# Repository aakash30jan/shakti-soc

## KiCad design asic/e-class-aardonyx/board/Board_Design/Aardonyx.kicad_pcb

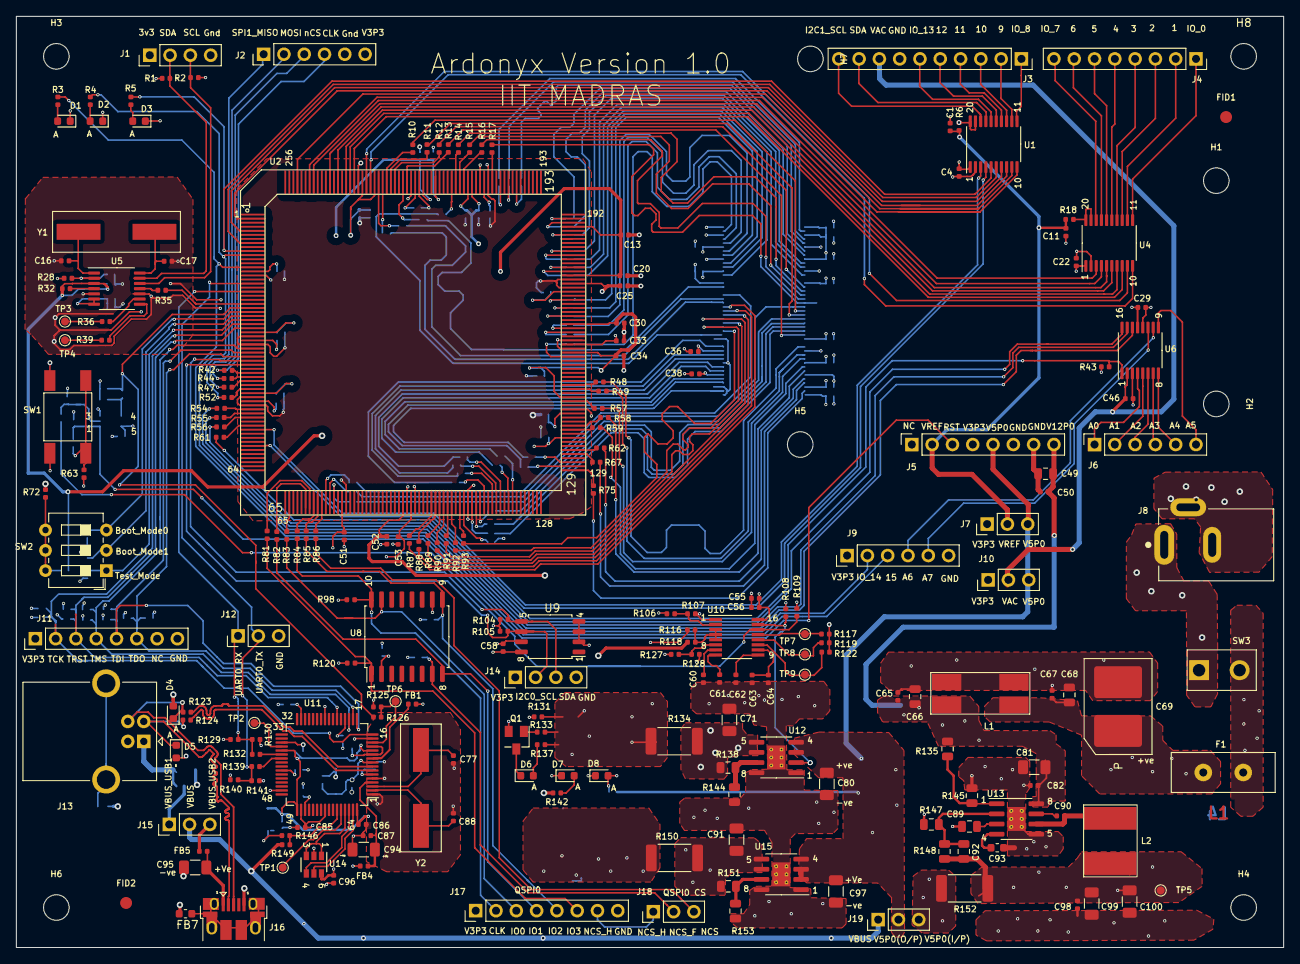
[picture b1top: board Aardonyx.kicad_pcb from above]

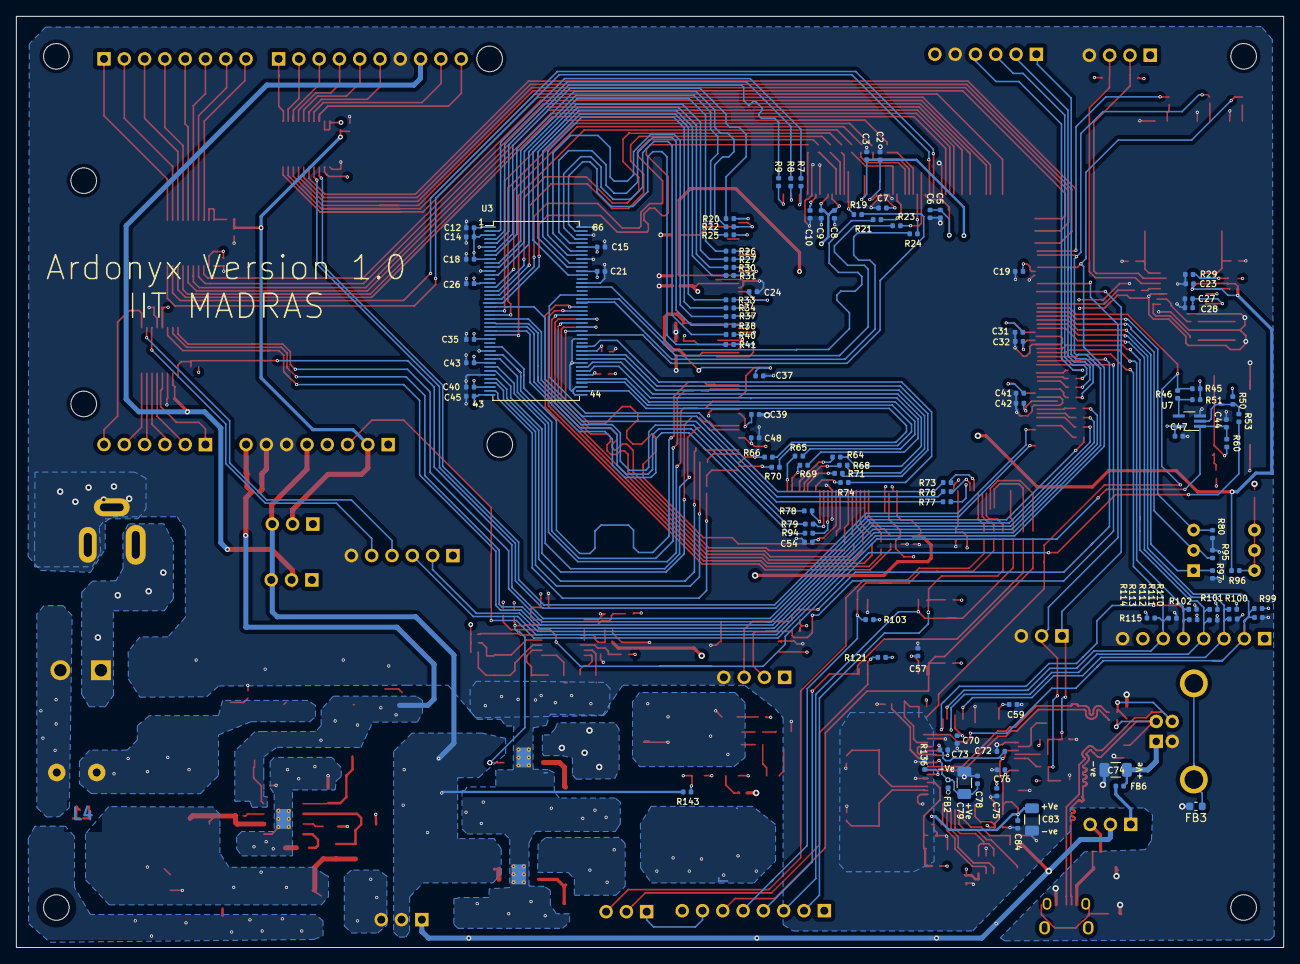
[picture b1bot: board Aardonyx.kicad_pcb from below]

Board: 4 copper layers, 158.6 x 116.5 mm, 330 parts (109 on the bottom side), 287 nets.

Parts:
C1, C2, C3, C4, C5, C6, C7, C8, C9, C10, C11, C12, C13, C14, C15, C18, C19, C20, C21, C22, C23, C24, C25, C26, C27, C28, C29, C30, C31, C32, C33, C34, C35, C36, C37, C38, C39, C40, C41, C42, C43, C44, C45, C46, C47, C48, C50, C51, C52, C53, C54, C55, C56, C57, C58, C59, C60, C61, C62, C63, C64, C65, C67, C70, C72, C73, C75, C76, C78, C82, C84, C85, C86, C87, C90, C96, C98: 0.1UF,0402; C_0402_1005Metric
C16, C17, C77, C88: 18PF,0402; C_0402_1005Metric
C49, C66, C68, C89: 1UF,0805; C_0805_2012Metric
C69: 220UF,2924; CP_EIA-2924_tcn4227_Pad6.1x7.3mm
C71, C91: 10UF,1206; C_1206_3216Metric
C74, C79, C80, C83, C94, C95, C97: 4.7UF,1206; C_1206_3216Metric
C81, C99, C100: 22UF,1206; C_1206_3216Metric
C92: 15PF,0805; C_0805_2012Metric
C93: 7500PF,0603; C_0603_1608Metric
D1, D2, D3, D6, D7, D8: LED,1206; LED_0603_1608Metric
D4, D5: CG0603MLC-12E; D_0603_1608Metric
F1: PTCCL13H921DBE; vishay_ptccl_d12.5mm_w4mm
FB1, FB2, FB4, FB5, FB6: 600E,FB,0402; L_0402_1005Metric
FB3, FB7: 47E,FB,0603; C_0603_1608Metric
FID1, FID2: Fiducial; Fiducial_1.5mm_Mask3mm
H1, H2, H3, H4, H5, H6, H7, H8: MountingHole; MountingHole_3.2mm_M3
J1, J14: Conn_1x4; PinHeader_1x04_P2.54mm_Vertical
J2, J9: Conn_1x6; PinHeader_1x06_P2.54mm_Vertical
J3: Conn_1x10_F; PinSocket_1x10_P2.54mm_Vertical
J4, J5: Conn_1x8_F; PinSocket_1x08_P2.54mm_Vertical
J6: Conn_1x6_F; PinSocket_1x06_P2.54mm_Vertical
J7, J10, J12, J15, J18, J19: Conn_1x3_M; PinHeader_1x03_P2.54mm_Vertical
J8: PJ-202H PWRJACK; CUI_PJ-202AH
J11, J17: Conn_1x8; PinHeader_1x08_P2.54mm_Vertical
J13: USB_B_6PIN; USB_B_OST_USB-B1HSxx_Horizontal
J16: USB_OTG; USB_Micro-B_Amphenol_10103594-0001LF_Horizontal
L1: CM3421Y600R-10; L_Laird_L9.55_W2.84
L2: 3.3UH; Bourns_srn8040ta_L8.5_W6.6
Q1: FDN339AN; SuperSOT-3
R1, R2, R28, R29, R32, R63, R106, R118, R128, R149: 4.7KE,0402; R_0402_1005Metric
R3, R4, R5, R142: 220E,0402; R_0402_1005Metric
R6, R18: 200KE,0402; R_0402_1005Metric
R7, R8, R9, R10, R11, R12, R13, R14, R15, R16, R17, R19, R20, R21, R22, R23, R24, R25, R26, R27, R30, R31, R33, R34, R35, R36, R37, R38, R39, R40, R41, R42, R44, R47, R48, R49, R52, R54, R55, R56, R57, R58, R59, R61, R62, R64, R65, R66, R67, R68, R69, R70, R71, R73, R74, R75, R76, R77, R78, R79, R81, R82, R83, R84, R85, R86, R87, R88, R89, R90, R91, R92, R93, R94, R123, R124: 22E,0402; R_0402_1005Metric
R43, R45, R50, R51, R80, R95, R97, R98, R103, R104, R105, R108, R109, R117, R119, R120, R121, R122, R146: 10KE,0402; R_0402_1005Metric
R46, R53, R72, R96, R126, R132, R139: 0E, 0402; R_0402_1005Metric
R60, R99, R100, R101, R102, R110, R111, R112, R113, R114, R115, R125, R129, R130, R131, R133, R140, R141, R143: 1KE,0402; R_0402_1005Metric
R107: 3.3kE, 0402; R_0402_1005Metric
R116, R127: 1.2kE, 0402; R_0402_1005Metric
R134, R150, R152: 0.02E,2512; R_2512_6332Metric
R135, R145: 10KE,0805; R_0805_2012Metric
R136: 12KE,0402; R_0402_1005Metric
R137: 120E,0402; R_0402_1005Metric
R138: 78.7KE,0805; R_0805_2012Metric
R144, R153: 30.1KE,0805; R_0805_2012Metric
R147: 22.1KE,0805; R_0805_2012Metric
R148: 124KE,0805; R_0805_2012Metric
R151: 169KE,0805; R_0805_2012Metric
SW1: FSM2JSMAATR; SW_PUSH_SPST_NO_4.5MM_7MM
SW2: SW_DIP_x03; SW_DIP_SPSTx03_Slide_6.7x9.18mm_W7.62mm_P2.54mm_LowProfile
SW3: SW_SPST; SW_toggle_spst_2.54mm
TP1, TP2, TP3, TP4, TP5, TP6: TestPoint; TestPoint_Pad_D1.0mm
TP7: OUT3; TestPoint_Pad_D1.0mm
TP8: OUT4; TestPoint_Pad_D1.0mm
TP9: POWER_GOOD; TestPoint_Pad_D1.0mm
U1, U4: LSF0108PWR; TSSOP-20_4.4x6.5mm_P0.65mm
U2: SKT32E; SKT32E_IITM
U3: IS42S32160F-TSOP2; TSSOP-II-86_10.16x22.2mm_P0.5mm
U5: CDCE913PW; TSSOP-14_4.4x5mm_P0.65mm
U6: ADC128S102CIMTX/NOPB; TSSOP-16_4.4x5mm_P0.65mm
U7: 74AUP1G09GW; SOT-353_SC-70-5_Handsoldering
U8: IS25LP256x-xM; SOIC-16W_7.5x10.3mm_P1.27mm
U9: CAT24M01XI-T2; SOIC-8_5.23x5.23mm_P1.27mm
U10: ADM1186; QSOP-16_3.9x4.9mm_P0.635mm
U11: FT2232H; LQFP-64_10x10mm_P0.5mm
U12, U15: TPS7A7002DDAR; SOIC-8-1EP_3.9x4.9mm_P1.27mm_EP2.29x3mm_ThermalVias
U13: TPS54627DDAR; SOIC-8-1EP_3.9x4.9mm_P1.27mm_EP2.29x3mm_ThermalVias
U14: 93LC56BT-I_OT; SOT-23-6
Y1: 27MHz; Crystal_SMD_ROHS_CSM_7XDN_HandSoldering
Y2: 12MHz; Crystal_SMD_ROHS_CSM_7XDN_HandSoldering

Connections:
/RESET: R45.2, R46.2, R126.1, U2.24
/arduino_header/A0: J6.1, U6.4
/arduino_header/A1: J6.2, U6.5
/arduino_header/A2: J6.3, U6.6
/arduino_header/A3: J6.4, U6.7
/arduino_header/A4: J6.5, U6.8
/arduino_header/A5: J6.6, U6.9
/arduino_header/A6: J9.4, U6.10
/arduino_header/A7: J9.5, U6.11
/arduino_header/AH_I2C1_SCL: J3.10, U1.18
/arduino_header/AH_I2C1_SDA: J3.9, U1.17
/arduino_header/AH_IO_0: J4.1, U4.11
/arduino_header/AH_IO_1: J4.2, U4.12
/arduino_header/AH_IO_2: J4.3, U4.13
/arduino_header/AH_IO_3: J4.4, U4.14
/arduino_header/AH_IO_4: J4.5, U4.15
/arduino_header/AH_IO_5: J4.6, U4.16
/arduino_header/AH_IO_6: J4.7, U4.17
/arduino_header/AH_IO_7: J4.8, U4.18
/arduino_header/AH_IO_8: J3.1, U1.11
/arduino_header/AH_IO_9: J3.2, U1.12
/arduino_header/AH_IO_10: J3.3, U1.13
/arduino_header/AH_IO_11: J3.4, U1.14
/arduino_header/AH_IO_12: J3.5, U1.15
/arduino_header/AH_IO_13: J3.6, U1.16
/arduino_header/I2C0_SCL: J14.2, R105.2, U2.38, U9.6
/arduino_header/I2C0_SDA: J14.3, R104.2, U2.37, U9.5
/arduino_header/I2C1_SCL: U1.3, U2.54
/arduino_header/I2C1_SDA: U1.4, U2.58
/arduino_header/IO_0: U2.235, U4.10
/arduino_header/IO_1: U2.236, U4.9
/arduino_header/IO_2: U2.239, U4.8
/arduino_header/IO_3: U2.240, U4.7
/arduino_header/IO_4: U2.241, U4.6
/arduino_header/IO_5: U2.243, U4.5
/arduino_header/IO_6: U2.245, U4.4
/arduino_header/IO_7: U2.249, U4.3
/arduino_header/IO_8: U1.10, U2.250
/arduino_header/IO_9: U1.9, U2.253
/arduino_header/IO_10: U1.8, U2.2
/arduino_header/IO_11: U1.7, U2.5
/arduino_header/IO_12: U1.6, U2.8
/arduino_header/IO_13: R5.1, U1.5, U2.10
/arduino_header/IO_14: J9.2, R4.1, U2.11
/arduino_header/IO_15: J9.3, R3.1, U2.14
/arduino_header/QSPI0_CLK: J17.2, R84.1, R98.1, U8.16
/arduino_header/QSPI0_IO0: J17.3, R83.1, U8.15
/arduino_header/QSPI0_IO1: J17.4, R82.1, U8.8
/arduino_header/QSPI0_IO2: J17.5, R85.1, R103.2, U8.9
/arduino_header/QSPI0_IO3: J17.6, R81.1, R120.2, U8.1
/arduino_header/QSPI0_NCS: J18.3, R86.1
/arduino_header/QSPI0_NCS_F: J18.2, R121.2, U8.7
/arduino_header/QSPI0_NCS_H: J17.7, J18.1
/arduino_header/RESET_AH: C44.1, J5.3, R60.2, U7.1
/arduino_header/SPI0_CLK: R56.2, U6.16
/arduino_header/SPI0_MISO: R55.2, U6.15
/arduino_header/SPI0_MOSI: R54.2, U6.14
/arduino_header/SPI0_nCS: R43.1, R61.2, U6.1
/arduino_header/SPI1_CLK: J2.4, R42.2
/arduino_header/SPI1_MISO: J2.1, R52.2
/arduino_header/SPI1_MOSI: J2.2, R47.2
/arduino_header/SPI1_nCS: J2.3, R44.2
/ftdi/D+: R123.1, U11.8
/ftdi/D-: R124.1, U11.7
/ftdi/FT_RESET: R125.2, R126.2, TP6.1, U11.14
/ftdi/PWRSAV: R146.1, R149.2, U11.59
/ftdi/TCK: J11.2, R99.2, R110.1, U2.28, U11.16
/ftdi/TDI: J11.5, R102.1, R113.2, U2.35, U11.17
/ftdi/TMS: J11.4, R101.2, R112.1, U2.34, U11.19
/ftdi/TRST: J11.3, R100.2, R111.1, U2.29, U11.22
/ftdi/UART0_RX: J12.1, R129.1, R130.2, R132.2, U2.20
/ftdi/UART0_TX: J12.2, R139.2, R140.1, R141.2, U2.18
/ftdi/USB_D+: D4.1, J13.3, J16.3, R123.2
/ftdi/USB_D-: D5.1, J13.2, J16.2, R124.2
/power_2/OUT3: R117.2, TP7.1, U10.13
/power_2/OUT4: R119.2, TP8.1, U10.12
/power_2/PWR_GOOD: R122.2, TP9.1, U10.11
/power_2/RESET_ASIC: R53.1, R109.2, U10.14
/power_2/UP_DOWN#: R127.2, R128.1, U10.6
/power_2/V1P8_MON: R116.1, R118.2, U10.3, U10.4, U10.5
/power_2/V3P3_MON: R106.2, R107.1, U10.2
/power_2/V18_EN: R108.2, U10.15, U12.2
/sdram/CLK: R35.1, U2.23
/sdram/SDRAM_A0: R78.2, U3.25
/sdram/SDRAM_A1: R79.2, U3.26
/sdram/SDRAM_A2: R94.2, U3.27
/sdram/SDRAM_A3: R93.2, U3.60
/sdram/SDRAM_A4: R92.2, U3.61
/sdram/SDRAM_A5: R91.2, U3.62
/sdram/SDRAM_A6: R90.2, U3.63
/sdram/SDRAM_A7: R89.2, U3.64
/sdram/SDRAM_A8: R88.2, U3.65
/sdram/SDRAM_A9: R87.2, U3.66
/sdram/SDRAM_A10: R77.2, U3.24
/sdram/SDRAM_A11: R76.2, U3.21
/sdram/SDRAM_A12: R73.2, U3.69
/sdram/SDRAM_BA0: R10.2, U3.22
/sdram/SDRAM_BA1: R11.2, U3.23
/sdram/SDRAM_CAS: R15.2, U3.18
/sdram/SDRAM_CKE: R24.2, U3.67
/sdram/SDRAM_CLK: R23.2, U3.68
/sdram/SDRAM_CS: R17.2, U3.20
/sdram/SDRAM_D0: R7.1, U3.2
/sdram/SDRAM_D1: R8.1, U3.4
/sdram/SDRAM_D2: R9.1, U3.5
/sdram/SDRAM_D3: R20.1, U3.7
/sdram/SDRAM_D4: R22.1, U3.8
/sdram/SDRAM_D5: R25.1, U3.10
/sdram/SDRAM_D6: R26.1, U3.11
/sdram/SDRAM_D7: R27.1, U3.13
/sdram/SDRAM_D8: R30.1, U3.74
/sdram/SDRAM_D9: R31.1, U3.76
/sdram/SDRAM_D10: R33.1, U3.77
/sdram/SDRAM_D11: R34.1, U3.79
/sdram/SDRAM_D12: R37.1, U3.80
/sdram/SDRAM_D13: R38.1, U3.82
/sdram/SDRAM_D14: R40.1, U3.83
/sdram/SDRAM_D15: R41.1, U3.85
/sdram/SDRAM_D16: R48.1, U3.31
/sdram/SDRAM_D17: R49.1, U3.33
/sdram/SDRAM_D18: R57.1, U3.34
/sdram/SDRAM_D19: R59.1, U3.36
/sdram/SDRAM_D20: R58.1, U3.37
/sdram/SDRAM_D21: R62.1, U3.39
/sdram/SDRAM_D22: R67.1, U3.40
/sdram/SDRAM_D23: R75.1, U3.42
/sdram/SDRAM_D24: R66.1, U3.45
/sdram/SDRAM_D25: R70.1, U3.47
/sdram/SDRAM_D26: R65.1, U3.48
/sdram/SDRAM_D27: R69.1, U3.50
/sdram/SDRAM_D28: R64.1, U3.51
/sdram/SDRAM_D29: R68.1, U3.53
/sdram/SDRAM_D30: R71.1, U3.54
/sdram/SDRAM_D31: R74.1, U3.56
/sdram/SDRAM_DQM0: R12.2, U3.16
/sdram/SDRAM_DQM1: R21.2, U3.71
/sdram/SDRAM_DQM2: R13.2, U3.28
/sdram/SDRAM_DQM3: R19.2, U3.59
/sdram/SDRAM_RAS: R16.2, U3.19
/sdram/SDRAM_WE: R14.2, U3.17
/soc/BOOT_MODE0: R80.1, SW2.3, U2.25
/soc/BOOT_MODE1: R95.1, SW2.2, U2.26
/soc/TD0: J11.6, R114.1, R115.2, U2.36, U11.18
/soc/TEST_MODE: R97.1, SW2.1, U2.27
GND: C1.2, C2.2, C3.2, C4.2, C5.2, C6.2, C7.2, C8.2, C9.2, C10.2, C11.2, C12.2, C13.2, C14.2, C15.2, C16.2, C17.2, C18.2, C19.2, C20.2, C21.2, C22.2, C23.2, C24.2, C25.2, C26.2, C27.2, C28.2, C29.2, C30.2, C31.2, C32.2, C33.2, C34.2, C35.2, C36.2, C37.2, C38.2, C39.2, C40.2, C41.2, C42.2, C43.2, C44.2, C45.2, C46.2, C47.2, C48.2, C49.2, C50.2, C51.2, C52.2, C53.2, C54.2, C55.2, C56.2, C57.2, C58.2, C59.2, C60.2, C61.2, C62.2, C63.2, C64.2, C65.2, C66.2, C67.2, C68.2, C69.2, C70.2, C71.2, C72.2, C73.2, C74.2, C75.1, C76.2, C77.2, C78.2, C79.2, C80.2, C81.2, C82.2, C83.2, C84.2, C85.2, C86.2, C87.2, C88.2, C89.2, C91.2, C93.2, C94.2, C95.2, C96.2, C97.2, C98.2, C99.2, C100.2, D1.1, D2.1, D3.1, D4.2, D5.2, D7.1, D8.1, FB1.2, FB3.2, FB7.1, J1.4, J2.5, J3.7, J5.6, J5.7, J8.2, J8.3, J9.6, J11.8, J12.3, J13.4, J14.4, J16.5, J17.8, L1.2, L1.3, Q1.2, R29.2, R80.2, R95.2, R97.2, R102.2, R107.2, R110.2, R111.2, R112.2, R114.2, R116.2, R128.2, R129.2, R131.2, R136.2, R140.2, R144.2, R145.2, R146.2, R147.2, R153.2, SW1.1, SW1.2, U1.1, U2.16, U2.31, U2.33, U2.46, U2.48, U2.80, U2.95, U2.97, U2.110, U2.144, U2.159, U2.161, U2.174, U2.176, U2.206, U2.208, U2.223, U2.225, U2.238, U3.6, U3.12, U3.32, U3.38, U3.44, U3.46, U3.52, U3.58, U3.72, U3.78, U3.84, U3.86, U4.1, U5.5, U5.10, U6.3, U6.12, U7.3, U8.10, U9.2, U9.3, U9.4, U9.7, U10.1, U11.1, U11.5, U11.11, U11.13, U11.15, U11.25, U11.35, U11.47, U11.51, U12.1, U12.8, U12.9, U13.5, U13.9, U14.2, U15.1, U15.8, U15.9
GNDA: FB1.1, U11.10
unnamed: C16.1, U5.1, Y1.2
unnamed: C17.1, U5.14, Y1.1
unnamed: C60.1, U10.7
unnamed: C61.1, U10.8
unnamed: C62.1, U10.9
unnamed: C63.1, C64.1, U10.10
unnamed: C67.1, C68.1, C69.1, F1.1, L1.1
unnamed: C71.1, R134.2, R138.1, U12.5, U12.6
unnamed: C74.1, FB6.1, J13.1
unnamed: C77.1, U11.3, Y2.2
unnamed: C78.1, C79.1, FB2.1, U11.9
unnamed: C87.1, C94.1, FB4.1, U11.4
unnamed: C88.1, U11.2, Y2.1
unnamed: C89.1, U13.3
unnamed: C90.1, U13.7
unnamed: C90.2, L2.1, U13.6
unnamed: C91.1, R150.2, R151.1, U15.5, U15.6
unnamed: C92.2, R147.1, R148.2, U13.2
unnamed: C93.1, U13.4
unnamed: C95.1, FB5.1, J16.1
unnamed: D1.2, R3.2
unnamed: D2.2, R4.2
unnamed: D3.2, R5.2
unnamed: D6.1, Q1.3
unnamed: D6.2, R137.2
unnamed: D7.2, R142.2
unnamed: D8.2, R143.2
unnamed: F1.2, SW3.3
unnamed: FB3.1, J13.5
unnamed: FB7.2, J16.6
unnamed: J1.2, R1.2, U5.13
unnamed: J1.3, R2.2, U5.12
unnamed: J8.1, SW3.1
unnamed: J19.3, R152.1
unnamed: Q1.1, R133.1
unnamed: R6.2, U1.19, U1.20
unnamed: R7.2, U2.203
unnamed: R8.2, U2.201
unnamed: R9.2, U2.199
unnamed: R10.1, U2.231
unnamed: R11.1, U2.230
unnamed: R12.1, U2.229
unnamed: R13.1, U2.226
unnamed: R14.1, U2.214
unnamed: R15.1, U2.213
unnamed: R16.1, U2.212
unnamed: R17.1, U2.205
unnamed: R18.2, U4.19, U4.20
unnamed: R19.1, U2.215
unnamed: R20.2, U2.191
unnamed: R21.1, U2.227
unnamed: R22.2, U2.190
unnamed: R23.1, U2.233
unnamed: R24.1, U2.232
unnamed: R25.2, U2.187
unnamed: R26.2, U2.183
unnamed: R27.2, U2.182
unnamed: R28.2, R29.1, U5.2
unnamed: R30.2, U2.179
unnamed: R31.2, U2.178
unnamed: R32.2, U5.4
unnamed: R33.2, U2.171
unnamed: R34.2, U2.169
unnamed: R35.2, U5.11
unnamed: R36.1, TP3.1
unnamed: R36.2, U5.9
unnamed: R37.2, U2.167
unnamed: R38.2, U2.164
unnamed: R39.1, TP4.1
unnamed: R39.2, U5.8
unnamed: R40.2, U2.163
unnamed: R41.2, U2.157
unnamed: R42.1, U2.40
unnamed: R44.1, U2.41
unnamed: R46.1, R51.2, U7.4
unnamed: R47.1, U2.42
unnamed: R48.2, U2.150
unnamed: R49.2, U2.149
unnamed: R50.2, R53.2, U7.2
unnamed: R52.1, U2.44
unnamed: R54.1, U2.49
unnamed: R55.1, U2.50
unnamed: R56.1, U2.51
unnamed: R57.2, U2.146
unnamed: R58.2, U2.140
unnamed: R59.2, U2.139
unnamed: R60.1, R63.2, SW1.3, SW1.4
unnamed: R61.1, U2.53
unnamed: R62.2, U2.134
unnamed: R64.2, U2.118
unnamed: R65.2, U2.121
unnamed: R66.2, U2.131
unnamed: R67.2, U2.133
unnamed: R68.2, U2.117
unnamed: R69.2, U2.120
unnamed: R70.2, U2.130
unnamed: R71.2, U2.116
unnamed: R72.2, R96.2, SW2.4, SW2.5, SW2.6
unnamed: R73.1, U2.75
unnamed: R74.2, U2.114
unnamed: R75.2, U2.129
unnamed: R76.1, U2.76
unnamed: R77.1, U2.77
unnamed: R78.1, U2.113
unnamed: R79.1, U2.112
unnamed: R81.2, U2.71
unnamed: R82.2, U2.70
unnamed: R83.2, U2.66
unnamed: R84.2, U2.72
unnamed: R85.2, U2.73
unnamed: R86.2, U2.74
unnamed: R87.1, U2.101
unnamed: R88.1, U2.102
unnamed: R89.1, U2.103
unnamed: R90.1, U2.104
unnamed: R91.1, U2.105
unnamed: R92.1, U2.106
unnamed: R93.1, U2.108
unnamed: R94.1, U2.111
unnamed: R132.1, U11.38
unnamed: R135.2, R145.1, U13.1
unnamed: R136.1, U11.6
unnamed: R138.2, R144.1, U12.7
unnamed: R139.1, U11.39
unnamed: R151.2, R153.1, U15.7
unnamed: TP1.1, U11.60
unnamed: TP2.1, U11.36
unnamed: U11.61, U14.1, U14.3
unnamed: U11.62, U14.4
unnamed: U11.63, U14.5
V1P8: C2.1, C3.1, C5.1, C6.1, C8.1, C9.1, C13.1, C20.1, C23.1, C24.1, C30.1, C31.1, C34.1, C37.1, C41.1, C48.1, C52.1, C54.1, R32.1, R96.1, R118.1, R131.1, R133.2, R134.1, R137.1, U2.30, U2.45, U2.94, U2.109, U2.137, U2.147, U2.158, U2.165, U2.173, U2.177, U2.189, U2.210, U2.211, U2.219, U2.222, U2.234, U2.237, U5.3
V3P3: C4.1, C7.1, C10.1, C12.1, C14.1, C15.1, C18.1, C19.1, C21.1, C22.1, C25.1, C26.1, C27.1, C28.1, C29.1, C32.1, C33.1, C35.1, C36.1, C38.1, C39.1, C40.1, C42.1, C43.1, C45.1, C47.1, C51.1, C53.1, C55.1, C56.1, C57.1, C58.1, C59.1, C70.1, C75.2, C76.1, C85.1, C96.1, FB2.2, FB4.2, J1.1, J2.6, J5.4, J7.1, J9.1, J10.1, J11.1, J14.1, J17.1, R1.1, R2.1, R28.1, R43.2, R45.1, R50.1, R51.1, R63.1, R72.1, R98.2, R99.1, R100.1, R101.1, R103.1, R104.1, R105.1, R106.1, R108.1, R109.1, R113.1, R115.1, R117.1, R119.1, R120.1, R121.1, R122.1, R125.1, R127.1, R130.1, R141.1, R142.1, R150.1, U1.2, U2.15, U2.32, U2.47, U2.79, U2.96, U2.143, U2.160, U2.175, U2.207, U2.224, U3.1, U3.3, U3.9, U3.15, U3.29, U3.35, U3.41, U3.43, U3.49, U3.55, U3.75, U3.81, U4.2, U5.6, U5.7, U6.13, U7.5, U8.2, U9.8, U10.16, U11.20, U11.31, U11.42, U11.50, U11.56, U14.6
V5P0: C80.1, C97.1, J5.5, J7.3, J10.3, J19.2, R143.1, U12.3, U12.4, U15.2, U15.3, U15.4
V12P0: C49.1, C50.1, C65.1, C66.1, C81.1, C82.1, J5.8, L1.4, R135.1, U13.8
VAC: C46.1, J3.8, J10.2, U6.2
VBUS: J15.2, J19.1, R149.1
VBUS_USB1: FB6.2, J15.1
VBUS_USB2: FB5.2, J15.3
VCC5V: C92.1, C98.1, C99.1, C100.1, L2.2, R148.1, R152.2, TP5.1
VCORE_FTDI: C72.1, C73.1, C83.1, C84.1, C86.1, U11.12, U11.37, U11.49, U11.64
VREF_AH: C1.1, C11.1, J5.2, J7.2, R6.1, R18.1

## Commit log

2020-07-08 update track drawing
2020-07-09 routing update
2020-07-09 updated track
2020-07-10 Updating power layer
2020-07-11 Update layout
2020-07-11 Layout update
2020-07-12 updated track fin
2020-07-13 Aardonyx.kicad_pcb
2020-07-13 update track & add the aardonyx project
2020-07-14 Updating layout
2020-07-14 updated ftdi track changes
2020-07-14 updated socket com placement
2020-07-14 diff tune for ftdi
2020-07-16 Which utility follows symbolic links right now in order to properly detect bluespec directory
2020-07-16 RAM routing update
2020-07-16 updated rechange address track
2020-07-16 Layout change
2020-07-18 update track
2020-07-19 updated new changes as per review
2020-07-21 updated tracks
2020-07-22 updated footprint & tracks
2020-07-25 Adding capacitors to clock
2020-07-25 updated footprint c37 & f1
2020-07-26 Updating layout after back annotation
2020-07-27 Updating symbols for USB
2020-07-28 updated silk screen
2020-07-28 updated silkscreen
2020-07-30 update socket compo placement
2020-07-31 updated socket foot print
2020-08-01 Updating power plane
2020-08-02 Adding Mounting hole
2020-08-02 updated mount hole
2020-08-02 update sock track & foot prin soc th
2020-08-03 updated drc error
2020-08-03 updated outline
2020-08-03 Adjusting edge.cuts
2020-08-04 Updating silk screen
2020-08-05 updated soc track
2020-08-06 Added VCU118 updated C-Class files and python configuration
2020-08-07 updated res cap silk screen commented by review
2020-08-07 Fixed constraints.xdc to reflect saferv original
2020-08-08 Final gerber files
2020-08-08 SDRAM Routing with Machine socket
2020-08-11 Updated layout
2020-08-11 updated foot print comp check
2020-08-12 Updating footprints
2020-08-13 updated soc back annotation
2020-08-14 Back annotation
2020-08-14 updated soc drc error
2020-08-14 Final layout files
2021-03-01 bump devices to 6.5.1
